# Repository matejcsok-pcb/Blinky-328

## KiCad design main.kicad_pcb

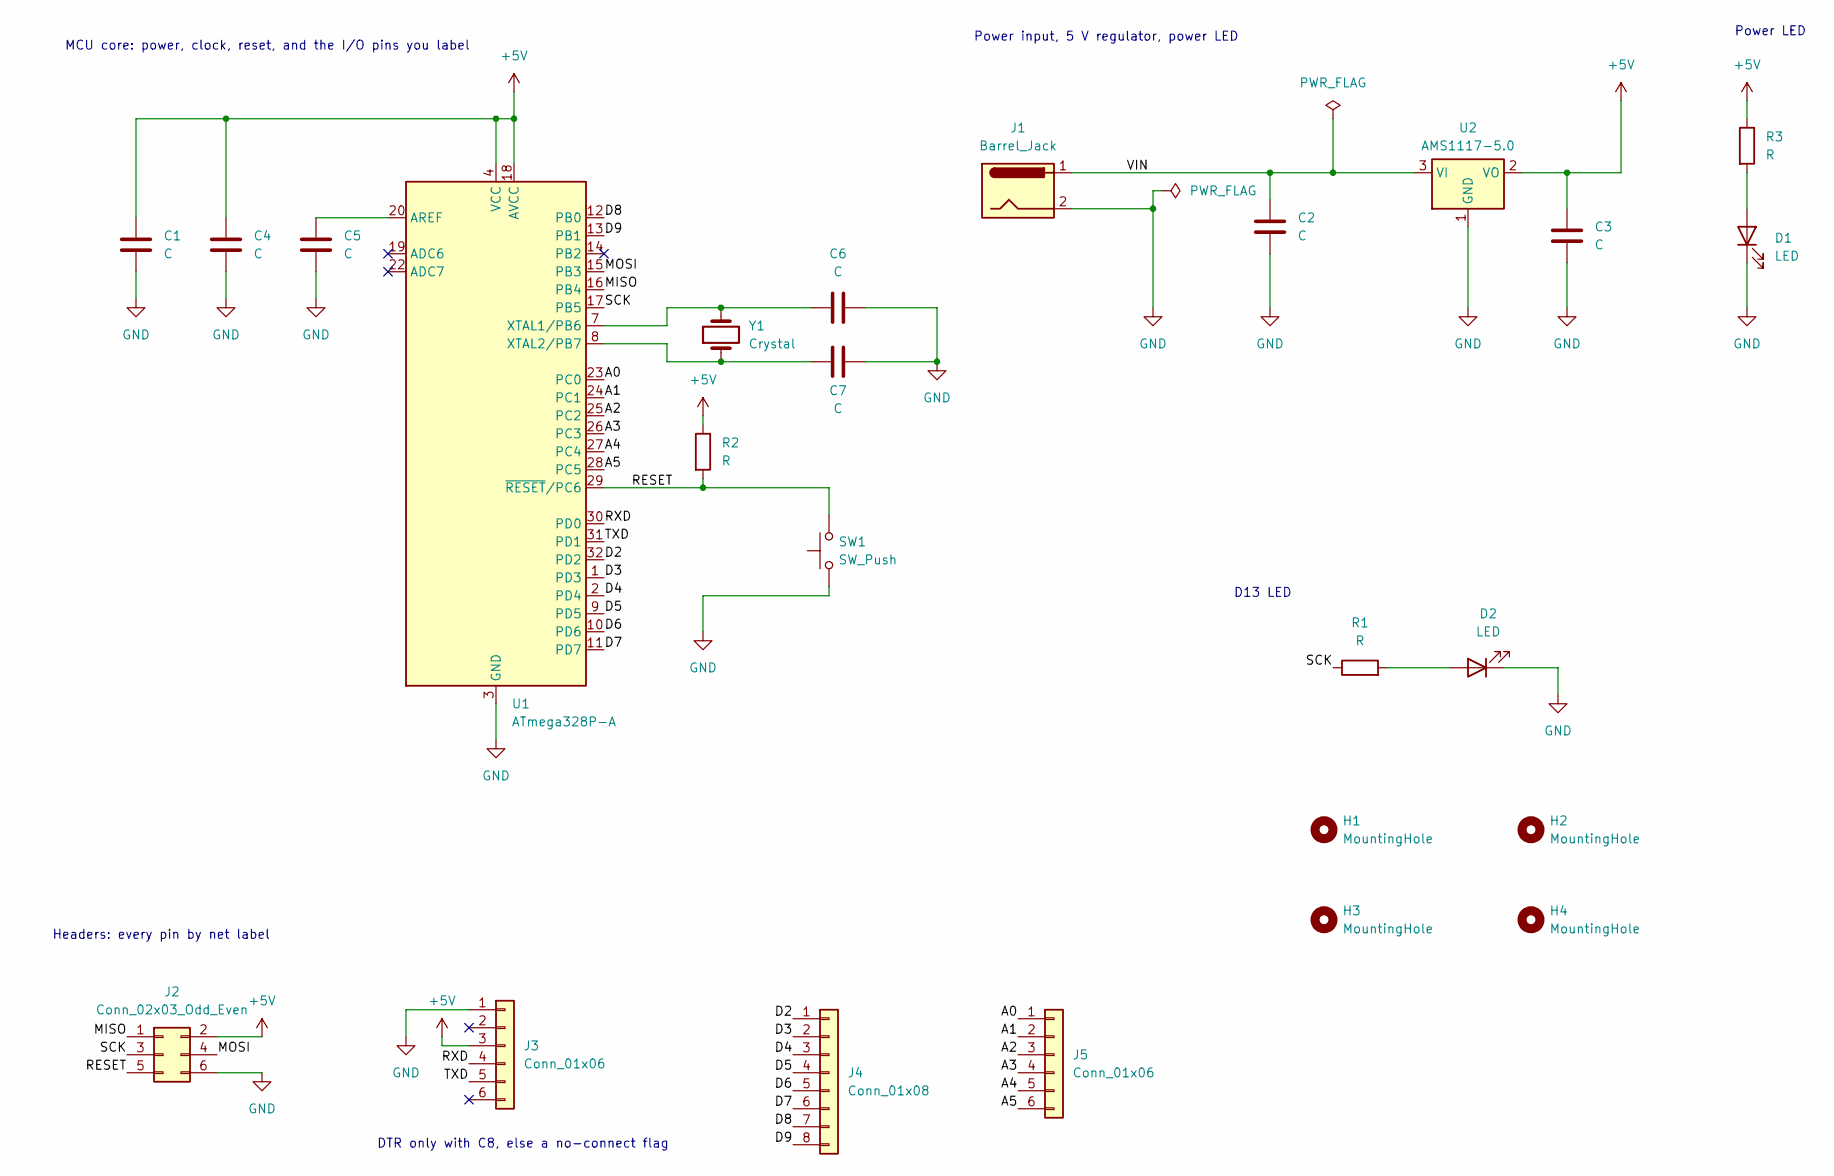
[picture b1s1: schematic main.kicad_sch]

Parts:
C1, C4, C5, C6, C7: C; C_0603_1608Metric
C2, C3: C; C_0805_2012Metric
D1, D2: LED; LED_0603_1608Metric
H1, H2, H3, H4: MountingHole; MountingHole_3.2mm_M3
J1: Barrel_Jack; BarrelJack_Horizontal
J2: Conn_02x03_Odd_Even; PinHeader_2x03_P2.54mm_Vertical
J3, J5: Conn_01x06; PinHeader_1x06_P2.54mm_Vertical
J4: Conn_01x08; PinHeader_1x08_P2.54mm_Vertical
R1, R2, R3: R; R_0603_1608Metric
SW1: SW_Push; SW_PUSH_6mm
U1: ATmega328P-A; TQFP-32_7x7mm_P0.8mm
U2: AMS1117-5.0; SOT-223-3_TabPin2
Y1: Crystal; Crystal_SMD_5032-2Pin_5.0x3.2mm

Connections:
+5V: C1.1, C3.1, C4.1, J2.2, J3.3, R2.1, R3.1, U1.4 (VCC), U1.6 (VCC), U1.18 (AVCC), U2.2 (VO)
/A0: J5.1, U1.23 (PC0)
/A1: J5.2, U1.24 (PC1)
/A2: J5.3, U1.25 (PC2)
/A3: J5.4, U1.26 (PC3)
/A4: J5.5, U1.27 (PC4)
/A5: J5.6, U1.28 (PC5)
/D2: J4.1, U1.32 (PD2)
/D3: J4.2, U1.1 (PD3)
/D4: J4.3, U1.2 (PD4)
/D5: J4.4, U1.9 (PD5)
/D6: J4.5, U1.10 (PD6)
/D7: J4.6, U1.11 (PD7)
/D8: J4.7, U1.12 (PB0)
/D9: J4.8, U1.13 (PB1)
/MISO: J2.1, U1.16 (PB4)
/MOSI: J2.4, U1.15 (PB3)
/RESET: J2.5, R2.2, SW1.2, U1.29 (~RESET/PC6)
/RXD: J3.4, U1.30 (PD0)
/SCK: J2.3, R1.1, U1.17 (PB5)
/TXD: J3.5, U1.31 (PD1)
/VIN: C2.1, J1.1, U2.3 (VI)
GND: C1.2, C2.2, C3.2, C4.2, C5.2, C6.2, C7.2, D1.1 (K), D2.1 (K), J1.2, J2.6, J3.1, SW1.1, U1.3 (GND), U1.5 (GND), U1.21 (GND), U2.1 (GND)
unnamed: D1.2 (A), R3.2
unnamed: D2.2 (A), R1.2
unnamed: C5.1, U1.20 (AREF)
unnamed: C6.1, U1.7 (XTAL1/PB6), Y1.2
unnamed: C7.1, U1.8 (XTAL2/PB7), Y1.1

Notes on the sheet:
Power input, 5 V regulator, power LED
Power LED
MCU core: power, clock, reset, and the I/O pins you label
Headers: every pin by net label
D13 LED
DTR only with C8, else a no-connect flag

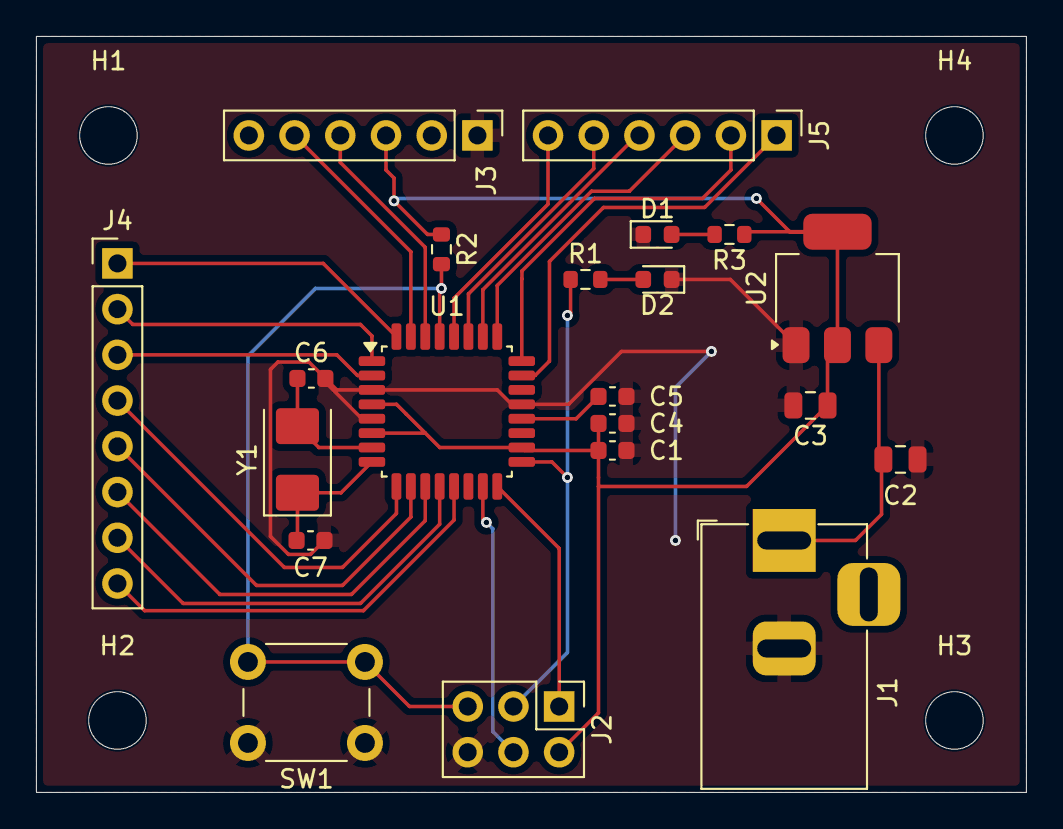
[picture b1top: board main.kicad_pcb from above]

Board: 2 copper layers, 55.0 x 42.0 mm, 25 parts (0 on the bottom side), 28 nets.
